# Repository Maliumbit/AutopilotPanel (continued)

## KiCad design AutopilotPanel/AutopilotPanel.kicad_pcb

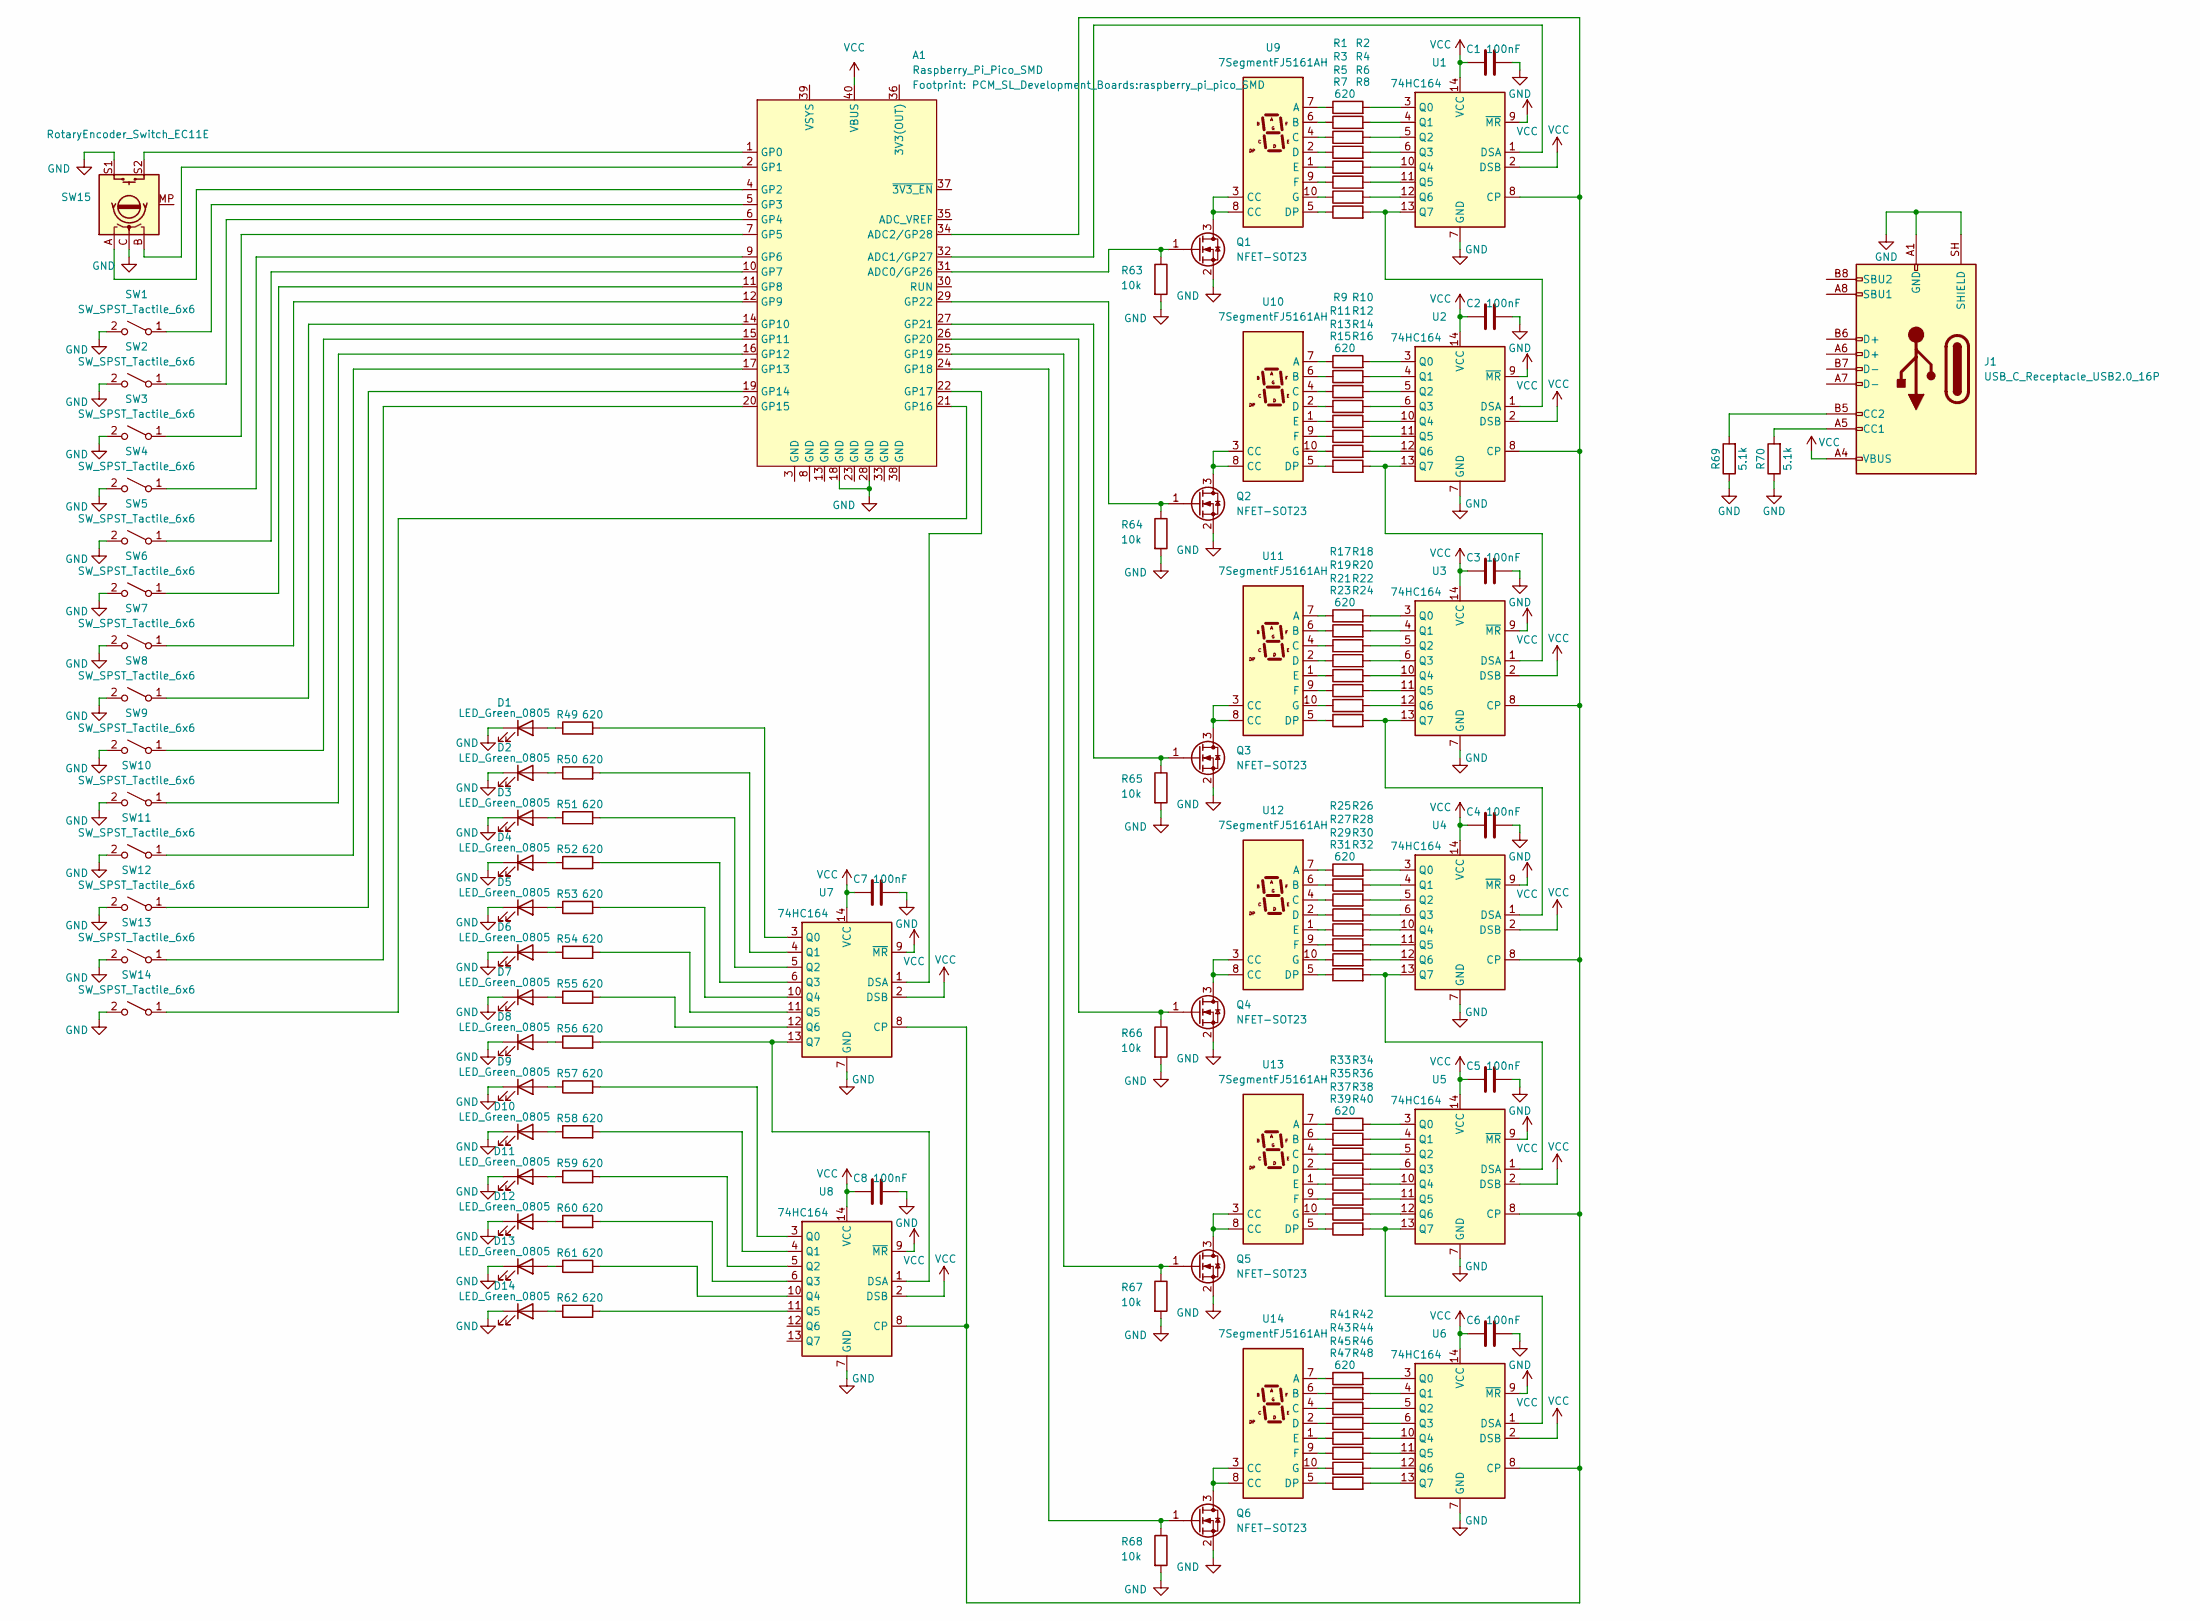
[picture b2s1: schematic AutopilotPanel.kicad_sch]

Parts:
A1: Raspberry_Pi_Pico_SMD; raspberry_pi_pico_SMD
C1, C2, C3, C4, C5, C6, C7, C8: 100nF; C_0805_2012Metric_Pad1.18x1.45mm_HandSolder
D1, D2, D3, D4, D5, D6, D7, D8, D9, D10, D11, D12, D13, D14: LED_Green_0805; LED_0805_2012Metric_Pad1.15x1.40mm_HandSolder
J1: USB_C_Receptacle_USB2.0_16P; USB_C_Receptacle_G-Switch_GT-USB-7010ASV
Q1, Q2, Q3, Q4, Q5, Q6: NFET-SOT23; SOT-23
R1, R2, R3, R4, R5, R6, R7, R8, R9, R10, R11, R12, R13, R14, R15, R16, R17, R18, R19, R20, R21, R22, R23, R24, R25, R26, R27, R28, R29, R30, R31, R32, R33, R34, R35, R36, R37, R38, R39, R40, R41, R42, R43, R44, R45, R46, R47, R48, R49, R50, R51, R52, R53, R54, R55, R56, R57, R58, R59, R60, R61, R62: 620; R_0805_2012Metric_Pad1.20x1.40mm_HandSolder
R63, R64, R65, R66, R67, R68: 10k; R_0805_2012Metric_Pad1.20x1.40mm_HandSolder
R69, R70: 5.1k; R_0805_2012Metric_Pad1.20x1.40mm_HandSolder
SW1, SW2, SW3, SW4, SW5, SW6, SW7, SW8, SW9, SW10, SW11, SW12, SW13, SW14: SW_SPST_Tactile_6x6; SW_Push_1P1T_NO_E-Switch_TL3301NxxxxxG
SW15: RotaryEncoder_Switch_EC11E; RotaryEncoder_Alps_EC11E-Switch_Vertical_H20mm
U1, U2, U3, U4, U5, U6, U7, U8: 74HC164; SOIC-14_3.9x8.7mm_P1.27mm
U9, U10, U11, U12, U13, U14: 7SegmentFJ5161AH; D1X8K

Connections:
GND: A1.18 (GND), A1.28 (GND), C1.2, C2.2, C3.2, C4.2, C5.2, C6.2, C7.2, C8.2, D1.1 (K), D2.1 (K), D3.1 (K), D4.1 (K), D5.1 (K), D6.1 (K), D7.1 (K), D8.1 (K), D9.1 (K), D10.1 (K), D11.1 (K), D12.1 (K), D13.1 (K), D14.1 (K), J1.A1 (GND), J1.A12 (GND), J1.B1 (GND), J1.B12 (GND), J1.SH (SHIELD), Q1.2 (S), Q2.2 (S), Q3.2 (S), Q4.2 (S), Q5.2 (S), Q6.2 (S), R63.2, R64.2, R65.2, R66.2, R67.2, R68.2, R69.1, R70.1, SW1.2 (B), SW2.2 (B), SW3.2 (B), SW4.2 (B), SW5.2 (B), SW6.2 (B), SW7.2 (B), SW8.2 (B), SW9.2 (B), SW10.2 (B), SW11.2 (B), SW12.2 (B), SW13.2 (B), SW14.2 (B), SW15.C, SW15.S1, U1.7 (GND), U2.7 (GND), U3.7 (GND), U4.7 (GND), U5.7 (GND), U6.7 (GND), U7.7 (GND), U8.7 (GND)
unnamed: A1.31 (ADC0/GP26), Q1.1 (G), R63.1
unnamed: A1.32 (ADC1/GP27), U1.1 (DSA)
unnamed: A1.34 (ADC2/GP28), U1.8 (CP), U2.8 (CP), U3.8 (CP), U4.8 (CP), U5.8 (CP), U6.8 (CP), U7.8 (CP), U8.8 (CP)
unnamed: A1.1 (GP0), SW15.S2
unnamed: A1.2 (GP1), SW15.B
unnamed: A1.4 (GP2), SW15.A
unnamed: A1.5 (GP3), SW1.1 (A)
unnamed: A1.6 (GP4), SW2.1 (A)
unnamed: A1.7 (GP5), SW3.1 (A)
unnamed: A1.9 (GP6), SW4.1 (A)
unnamed: A1.10 (GP7), SW5.1 (A)
unnamed: A1.11 (GP8), SW6.1 (A)
unnamed: A1.12 (GP9), SW7.1 (A)
unnamed: A1.14 (GP10), SW8.1 (A)
unnamed: A1.15 (GP11), SW9.1 (A)
unnamed: A1.16 (GP12), SW10.1 (A)
unnamed: A1.17 (GP13), SW11.1 (A)
unnamed: A1.19 (GP14), SW12.1 (A)
unnamed: A1.20 (GP15), SW13.1 (A)
unnamed: A1.21 (GP16), SW14.1 (A)
unnamed: A1.22 (GP17), U7.1 (DSA)
unnamed: A1.24 (GP18), Q6.1 (G), R68.1
unnamed: A1.25 (GP19), Q5.1 (G), R67.1
unnamed: A1.26 (GP20), Q4.1 (G), R66.1
unnamed: A1.27 (GP21), Q3.1 (G), R65.1
unnamed: A1.29 (GP22), Q2.1 (G), R64.1
unnamed: D1.2 (A), R49.1
unnamed: D2.2 (A), R50.1
unnamed: D3.2 (A), R51.1
unnamed: D4.2 (A), R52.1
unnamed: D5.2 (A), R53.1
unnamed: D6.2 (A), R54.1
unnamed: D7.2 (A), R55.1
unnamed: D8.2 (A), R56.1
unnamed: D9.2 (A), R57.1
unnamed: D10.2 (A), R58.1
unnamed: D11.2 (A), R59.1
unnamed: D12.2 (A), R60.1
unnamed: D13.2 (A), R61.1
unnamed: D14.2 (A), R62.1
unnamed: J1.A5 (CC1), R70.2
unnamed: J1.B5 (CC2), R69.2
unnamed: Q1.3 (D), U9.3 (CC), U9.8 (CC)
unnamed: Q2.3 (D), U10.3 (CC), U10.8 (CC)
unnamed: Q3.3 (D), U11.3 (CC), U11.8 (CC)
unnamed: Q4.3 (D), U12.3 (CC), U12.8 (CC)
unnamed: Q5.3 (D), U13.3 (CC), U13.8 (CC)
unnamed: Q6.3 (D), U14.3 (CC), U14.8 (CC)
unnamed: R1.2, U1.3 (Q0)
unnamed: R2.2, U1.4 (Q1)
unnamed: R3.2, U1.5 (Q2)
unnamed: R4.2, U1.6 (Q3)
unnamed: R5.2, U1.10 (Q4)
unnamed: R6.2, U1.11 (Q5)
unnamed: R7.2, U1.12 (Q6)
unnamed: R8.2, U1.13 (Q7), U2.1 (DSA)
unnamed: R9.2, U2.3 (Q0)
unnamed: R10.2, U2.4 (Q1)
unnamed: R11.2, U2.5 (Q2)
unnamed: R12.2, U2.6 (Q3)
unnamed: R13.2, U2.10 (Q4)
unnamed: R14.2, U2.11 (Q5)
unnamed: R15.2, U2.12 (Q6)
unnamed: R16.2, U2.13 (Q7), U3.1 (DSA)
unnamed: R17.2, U3.3 (Q0)
unnamed: R18.2, U3.4 (Q1)
unnamed: R19.2, U3.5 (Q2)
unnamed: R20.2, U3.6 (Q3)
unnamed: R21.2, U3.10 (Q4)
unnamed: R22.2, U3.11 (Q5)
unnamed: R23.2, U3.12 (Q6)
unnamed: R24.2, U3.13 (Q7), U4.1 (DSA)
unnamed: R25.2, U4.3 (Q0)
unnamed: R26.2, U4.4 (Q1)
unnamed: R27.2, U4.5 (Q2)
unnamed: R28.2, U4.6 (Q3)
unnamed: R29.2, U4.10 (Q4)
unnamed: R30.2, U4.11 (Q5)
unnamed: R31.2, U4.12 (Q6)
unnamed: R32.2, U4.13 (Q7), U5.1 (DSA)
unnamed: R33.2, U5.3 (Q0)
unnamed: R34.2, U5.4 (Q1)
unnamed: R35.2, U5.5 (Q2)
unnamed: R36.2, U5.6 (Q3)
unnamed: R37.2, U5.10 (Q4)
unnamed: R38.2, U5.11 (Q5)
unnamed: R39.2, U5.12 (Q6)
unnamed: R40.2, U5.13 (Q7), U6.1 (DSA)
unnamed: R41.2, U6.3 (Q0)
unnamed: R42.2, U6.4 (Q1)
unnamed: R43.2, U6.5 (Q2)
unnamed: R44.2, U6.6 (Q3)
unnamed: R45.2, U6.10 (Q4)
unnamed: R46.2, U6.11 (Q5)
unnamed: R47.2, U6.12 (Q6)
unnamed: R48.2, U6.13 (Q7)
unnamed: R49.2, U7.3 (Q0)
unnamed: R50.2, U7.4 (Q1)
unnamed: R51.2, U7.5 (Q2)
unnamed: R52.2, U7.6 (Q3)
unnamed: R53.2, U7.10 (Q4)
unnamed: R54.2, U7.11 (Q5)
unnamed: R55.2, U7.12 (Q6)
unnamed: R56.2, U7.13 (Q7), U8.1 (DSA)
unnamed: R57.2, U8.3 (Q0)
unnamed: R58.2, U8.4 (Q1)
unnamed: R59.2, U8.5 (Q2)
unnamed: R60.2, U8.6 (Q3)
unnamed: R61.2, U8.10 (Q4)
unnamed: R62.2, U8.11 (Q5)
unnamed: R1.1, U9.7 (A)
unnamed: R2.1, U9.6 (B)
unnamed: R3.1, U9.4 (C)
unnamed: R4.1, U9.2 (D)
unnamed: R8.1, U9.5 (DP)
unnamed: R5.1, U9.1 (E)
unnamed: R6.1, U9.9 (F)
unnamed: R7.1, U9.10 (G)
unnamed: R9.1, U10.7 (A)
unnamed: R10.1, U10.6 (B)
unnamed: R11.1, U10.4 (C)
unnamed: R12.1, U10.2 (D)
unnamed: R16.1, U10.5 (DP)
unnamed: R13.1, U10.1 (E)
unnamed: R14.1, U10.9 (F)
unnamed: R15.1, U10.10 (G)
unnamed: R17.1, U11.7 (A)
unnamed: R18.1, U11.6 (B)
unnamed: R19.1, U11.4 (C)
unnamed: R20.1, U11.2 (D)
unnamed: R24.1, U11.5 (DP)
unnamed: R21.1, U11.1 (E)
unnamed: R22.1, U11.9 (F)
unnamed: R23.1, U11.10 (G)
unnamed: R25.1, U12.7 (A)
unnamed: R26.1, U12.6 (B)
unnamed: R27.1, U12.4 (C)
unnamed: R28.1, U12.2 (D)
unnamed: R32.1, U12.5 (DP)
unnamed: R29.1, U12.1 (E)
unnamed: R30.1, U12.9 (F)
unnamed: R31.1, U12.10 (G)
unnamed: R33.1, U13.7 (A)
unnamed: R34.1, U13.6 (B)
unnamed: R35.1, U13.4 (C)
unnamed: R36.1, U13.2 (D)
unnamed: R40.1, U13.5 (DP)
unnamed: R37.1, U13.1 (E)
unnamed: R38.1, U13.9 (F)
unnamed: R39.1, U13.10 (G)
unnamed: R41.1, U14.7 (A)
unnamed: R42.1, U14.6 (B)
unnamed: R43.1, U14.4 (C)
unnamed: R44.1, U14.2 (D)
unnamed: R48.1, U14.5 (DP)
unnamed: R45.1, U14.1 (E)
unnamed: R46.1, U14.9 (F)
unnamed: R47.1, U14.10 (G)
VCC: A1.40 (VBUS), C1.1, C2.1, C3.1, C4.1, C5.1, C6.1, C7.1, C8.1, J1.A4 (VBUS), J1.A9 (VBUS), J1.B4 (VBUS), J1.B9 (VBUS), U1.2 (DSB), U1.9 (~MR), U1.14 (VCC), U2.2 (DSB), U2.9 (~MR), U2.14 (VCC), U3.2 (DSB), U3.9 (~MR), U3.14 (VCC), U4.2 (DSB), U4.9 (~MR), U4.14 (VCC), U5.2 (DSB), U5.9 (~MR), U5.14 (VCC), U6.2 (DSB), U6.9 (~MR), U6.14 (VCC), U7.2 (DSB), U7.9 (~MR), U7.14 (VCC), U8.2 (DSB), U8.9 (~MR), U8.14 (VCC)

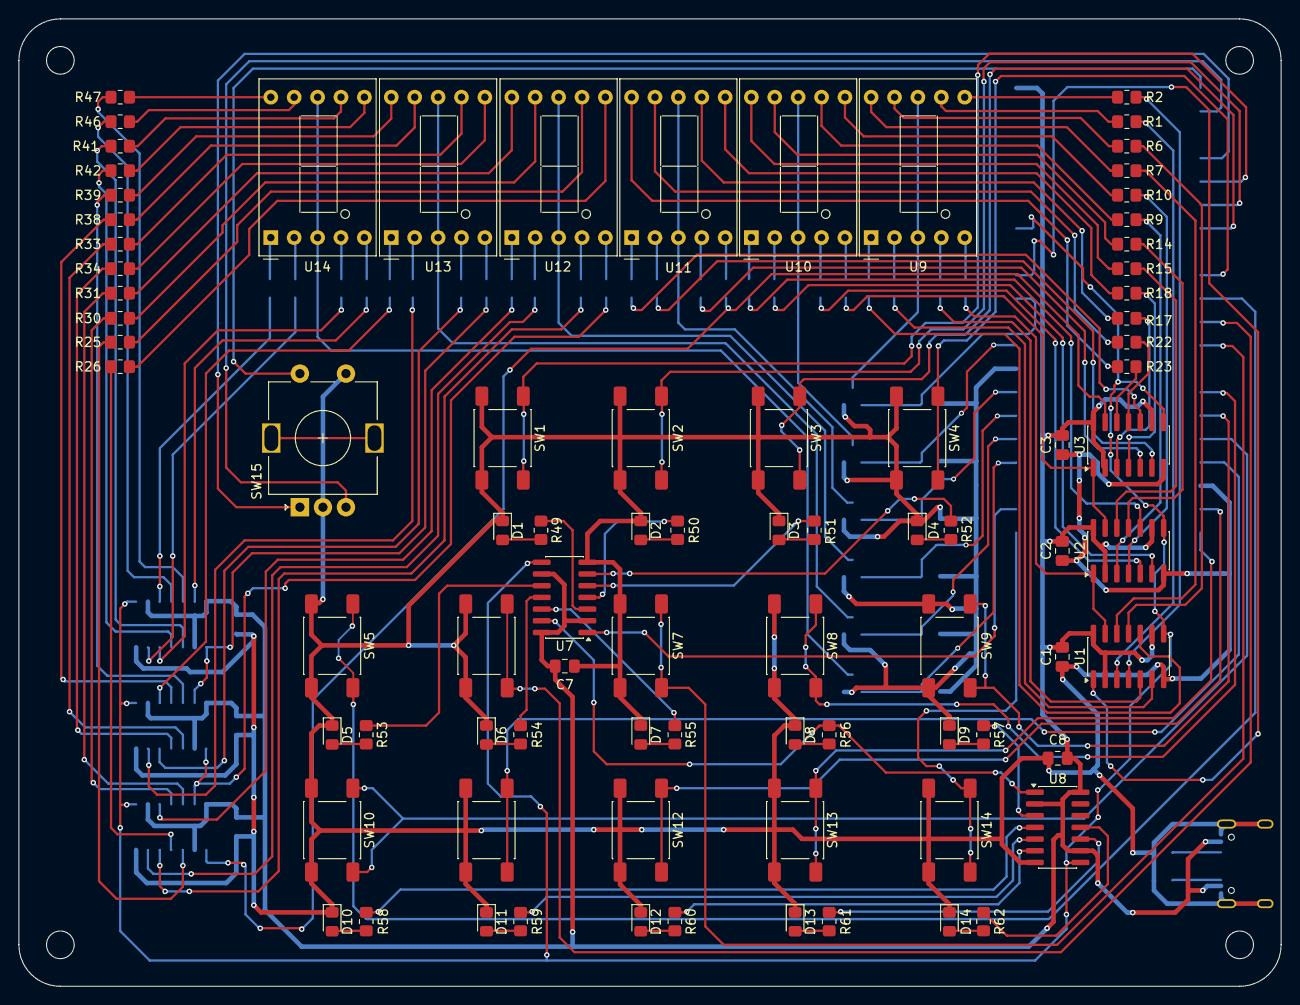
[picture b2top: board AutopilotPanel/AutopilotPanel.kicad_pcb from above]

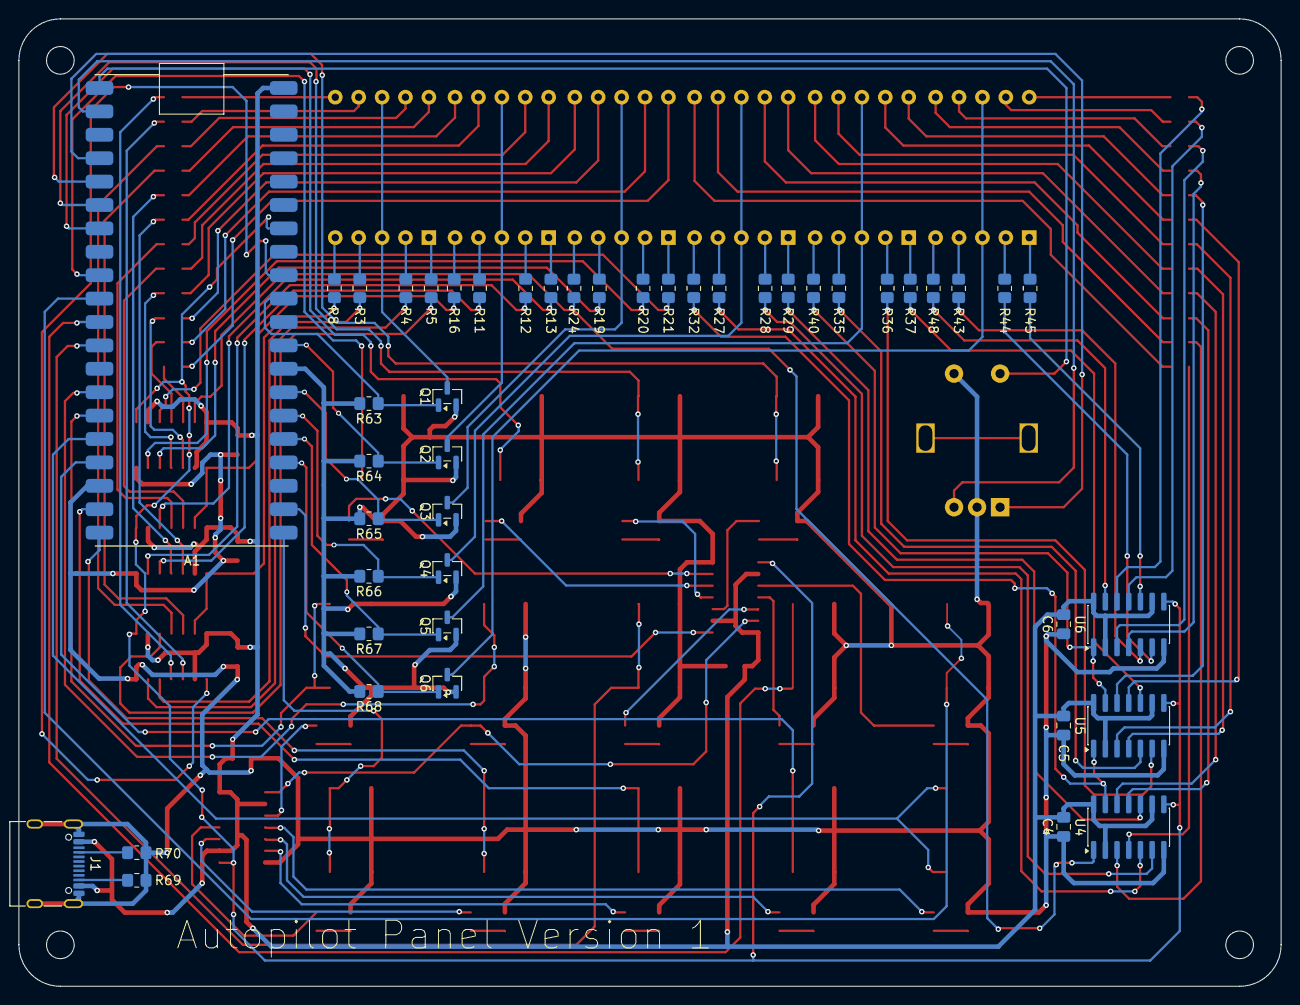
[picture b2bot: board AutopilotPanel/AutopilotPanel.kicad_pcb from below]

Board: 2 copper layers, 137.0 x 105.0 mm, 129 parts (46 on the bottom side), 160 nets.
